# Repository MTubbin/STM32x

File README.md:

# STM32x
Repo for custom STM32F4 Breakout board 

Directory:

Hardware folder - PCB Schematic, board layout
  - Photos: Schematic, PCB, and Board Photos

Software folder - current main and display txt files

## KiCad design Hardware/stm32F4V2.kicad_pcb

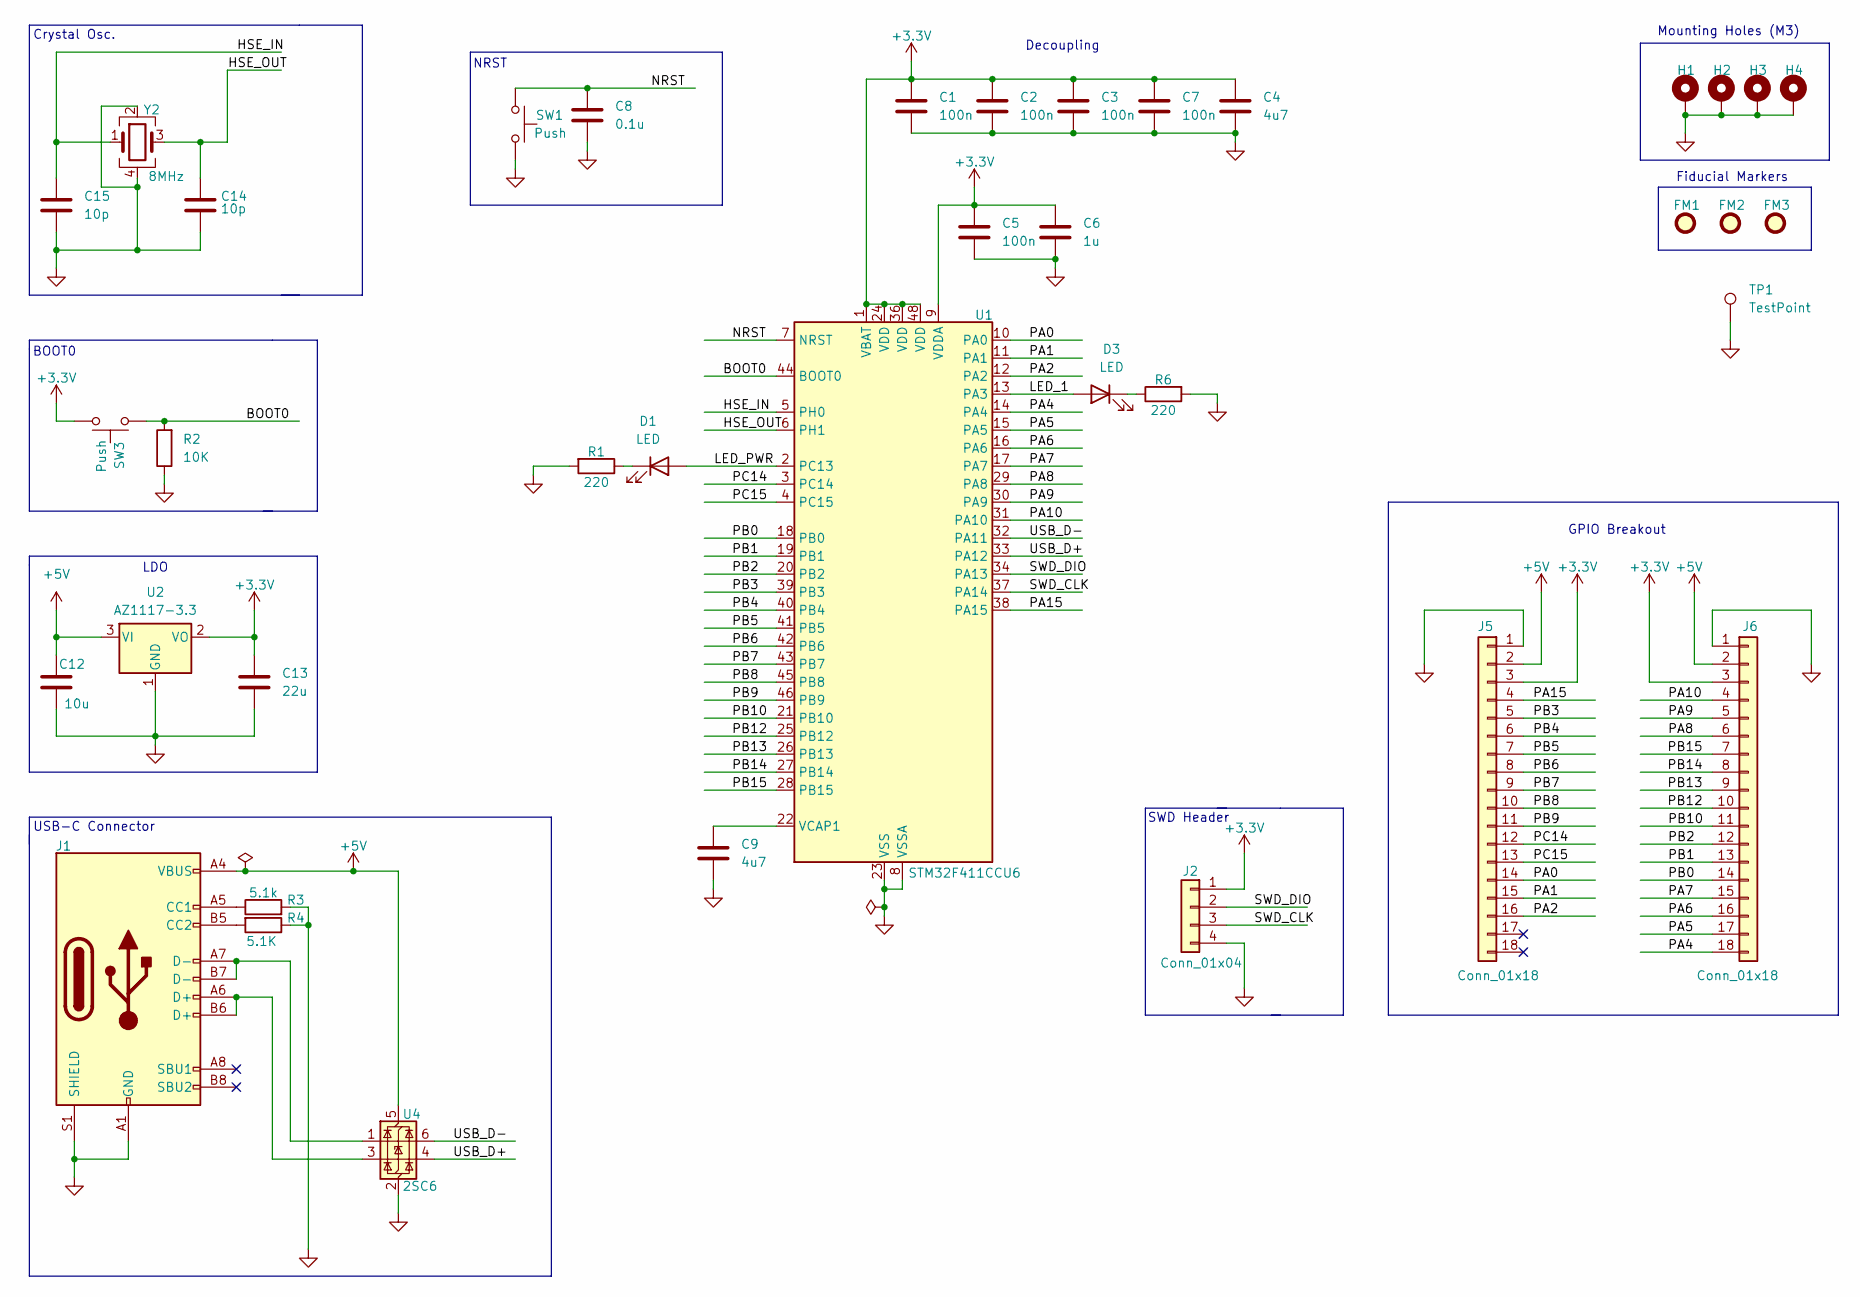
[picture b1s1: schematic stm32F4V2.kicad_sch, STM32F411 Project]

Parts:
C1, C2, C3, C5, C7: 100n; C_0402_1005Metric; Manufacturer Part Number 04023C104KAT2A-62
C4, C9: 4u7; C_0603_1608Metric; Manufacturer Part Number C1608X5R1C475K080AC
C6: 1u; C_0402_1005Metric; Manufacturer Part Number GRM155R70J105KA12D
C8: 0.1u; C_0402_1005Metric; Manufacturer Part Number 0402B104K160HI
C12: 10u; C_0603_1608Metric; Manufacturer Part Number CL10A106MQ8NNNC
C13: 22u; C_0603_1608Metric; Manufacturer Part Number GRM188R60J226MEA0D
C14, C15: 10p; C_0402_1005Metric; Manufacturer Part Number 885012005007
D1, D3: LED; LED_0402_1005Metric; Manufacturer Part Number YY0402RE-NN2S0-T1AR4
FM1, FM2, FM3: Fiducial; Fiducial_1mm_Mask2mm
H1, H2, H3, H4: MountingHole_Pad; MountingHole_2.2mm_M2_Pad_Via
J1: USB_C_Receptacle_USB2.0_16P; USB_C_Receptacle_GCT_USB4105-xx-A_16P_TopMnt_Horizontal; Manufacturer Part Number USB4105-GF-A
J2: Conn_01x04; PinHeader_1x04_P2.54mm_Vertical; Manufacturer Part Number 61300411121
J5, J6: Conn_01x18; PinHeader_1x18_P2.54mm_Vertical; Manufacturer Part Number PH1-18-UA
R1, R6: 220; R_0402_1005Metric; Manufacturer Part Number RC0402FR-07221RL
R2: 10K; R_0402_1005Metric; Manufacturer Part Number RC0402JR-0710KL
R3: 5.1k; R_0402_1005Metric; Manufacturer Part Number RC0402FR-075K1L
R4: 5.1K; R_0402_1005Metric; Manufacturer Part Number RC0402FR-075K1L
SW1, SW3: Push; SW_SPST_B3U-1000P; Manufacturer Part Number B3U-1000P-B
TP1: TestPoint; TestPoint_Pad_2.0x2.0mm
U1: STM32F411CCU6; QFN-48-1EP_7x7mm_P0.5mm_EP5.6x5.6mm; Manufacturer Part Number STM32F411CCU6TR
U2: AZ1117-3.3; SOT-223-3_TabPin2; Manufacturer Part Number AZ1117CH-3.3TRG1
U4: 2SC6; SOT-23-6; Manufacturer Part Number USBLC6-2SC6
Y2: 8MHz; Crystal_SMD_Abracon_ABM8G-4Pin_3.2x2.5mm; Manufacturer Part Number ABM8G-16.000MHZ-4Y-T3

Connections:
+3.3V: C1.1, C2.1, C3.1, C4.1, C5.1, C6.1, C7.1, C13.1, J2.1, J5.3, J6.3, SW3.2, U1.1 (VBAT), U1.9 (VDDA), U1.24 (VDD), U1.36 (VDD), U1.48 (VDD), U2.2 (VO)
+5V: C12.1, J1.A4 (VBUS), J1.A9 (VBUS), J1.B4 (VBUS), J1.B9 (VBUS), J5.2, J6.2, U2.3 (VI), U4.5 (VBUS)
/BOOT0: R2.2, SW3.1, U1.44 (BOOT0)
/HSE_IN: C15.1, U1.5 (PH0), Y2.1
/HSE_OUT: C14.1, U1.6 (PH1), Y2.3
/LED_1: D3.2 (A), U1.13 (PA3)
/LED_PWR: D1.2 (A), U1.2 (PC13)
/NRST: C8.2, SW1.1, U1.7 (NRST)
/PA0: J5.14, U1.10 (PA0)
/PA1: J5.15, U1.11 (PA1)
/PA2: J5.16, U1.12 (PA2)
/PA4: J6.18, U1.14 (PA4)
/PA5: J6.17, U1.15 (PA5)
/PA6: J6.16, U1.16 (PA6)
/PA7: J6.15, U1.17 (PA7)
/PA8: J6.6, U1.29 (PA8)
/PA9: J6.5, U1.30 (PA9)
/PA10: J6.4, U1.31 (PA10)
/PA15: J5.4, U1.38 (PA15)
/PB0: J6.14, U1.18 (PB0)
/PB1: J6.13, U1.19 (PB1)
/PB2: J6.12, U1.20 (PB2)
/PB3: J5.5, U1.39 (PB3)
/PB4: J5.6, U1.40 (PB4)
/PB5: J5.7, U1.41 (PB5)
/PB6: J5.8, U1.42 (PB6)
/PB7: J5.9, U1.43 (PB7)
/PB8: J5.10, U1.45 (PB8)
/PB9: J5.11, U1.46 (PB9)
/PB10: J6.11, U1.21 (PB10)
/PB12: J6.10, U1.25 (PB12)
/PB13: J6.9, U1.26 (PB13)
/PB14: J6.8, U1.27 (PB14)
/PB15: J6.7, U1.28 (PB15)
/PC14: J5.12, U1.3 (PC14)
/PC15: J5.13, U1.4 (PC15)
/SWD_CLK: J2.3, U1.37 (PA14)
/SWD_DIO: J2.2, U1.34 (PA13)
/USB_D+: U1.33 (PA12), U4.4 (I/O2)
/USB_D-: U1.32 (PA11), U4.6 (I/O1)
GND: C1.2, C2.2, C3.2, C4.2, C5.2, C6.2, C7.2, C8.1, C9.2, C12.2, C13.2, C14.2, C15.2, H1.1, H2.1, H3.1, H4.1, J1.A1 (GND), J1.A12 (GND), J1.B1 (GND), J1.B12 (GND), J1.S1 (SHIELD), J2.4, J5.1, J6.1, R1.2, R2.1, R3.2, R4.1, R6.2, SW1.2, TP1.1, U1.8 (VSSA), U1.23 (VSS), U1.35 (VSS), U1.47 (VSS), U1.49 (VSS), U2.1 (GND), U4.2 (GND), Y2.2, Y2.4
unnamed: D1.1 (K), R1.1
unnamed: D3.1 (K), R6.1
unnamed: J1.A5 (CC1), R3.1
unnamed: J1.B5 (CC2), R4.2
unnamed: J1.A6 (D+), J1.B6 (D+), U4.3 (I/O2)
unnamed: J1.A7 (D-), J1.B7 (D-), U4.1 (I/O1)
unnamed: C9.1, U1.22 (VCAP1)

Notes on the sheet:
USB-C Connector
NRST
BOOT0
Crystal Osc.
Decoupling
LDO
Mounting Holes (M3)
GPIO Breakout
Fiducial Markers
SWD Header

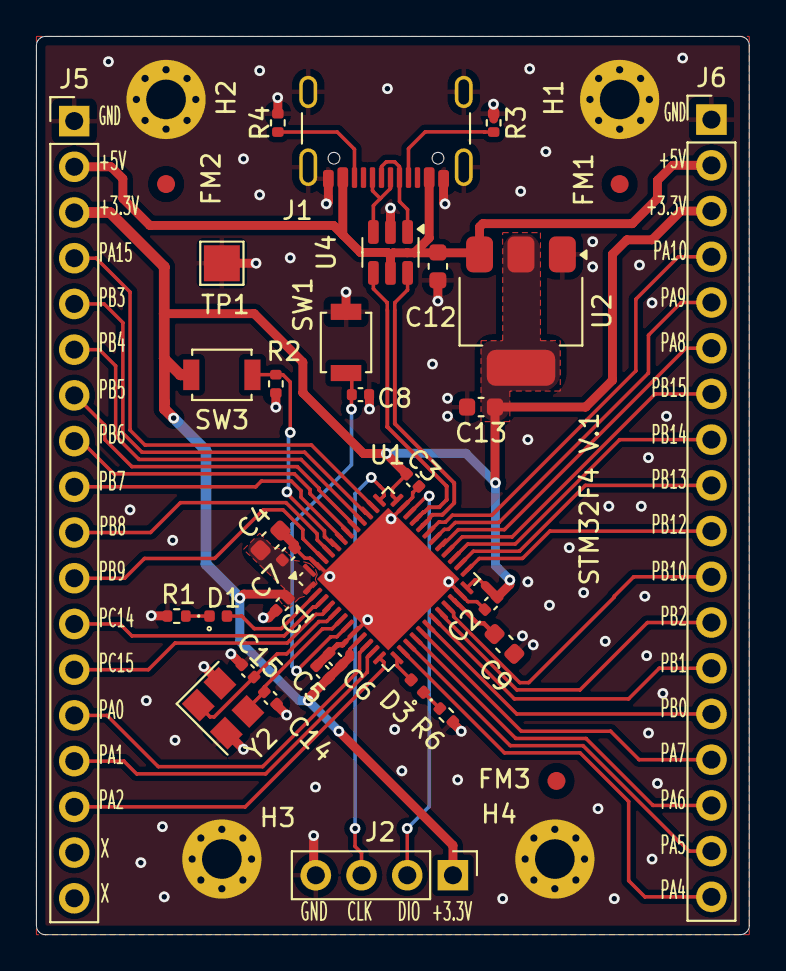
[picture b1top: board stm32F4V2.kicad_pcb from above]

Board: 2 copper layers, 39.6 x 49.9 mm, 38 parts (0 on the bottom side), 48 nets.

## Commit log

2024-12-17 Added KiCad files with initial development
2024-12-19 Added GPIO Breakout and SWD Conn.
2024-12-24 Added Footprints and Parts list
2024-12-25 Added Initial PCB Layout
2024-12-25 Added Net Labels and refined Footprints
2024-12-30 PCB Layout Rough Draft and Schematic Changes
2025-01-01 Revised board layout
2025-01-02 Finalized Layout for V.1
2025-01-27 Added Board and Schematic Photos
2025-02-17 Added current software
2025-02-17 added photos
